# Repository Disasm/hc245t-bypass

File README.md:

# `hc245t-bypass`

This tiny board is useful to replace 74HC245T chips on Colorlight 5A-75B and 5A-75E boards.

You can order these boards from OSH Park: https://oshpark.com/shared_projects/Og8YtGBU Don't forget to select Flex board type on the order page!

## Rework

The board needs some rework to improve solderability. It's also possible to solder it "as is", but you can encounter shorts between the adjacent pins.

First, separate the boards from a panel. This can be done easily with scissors.

Next, cut each board by the line marked in red. The line should be on the edge of each via, not on the center. Try to make the line as straight as possible. The idea is to cut as much copper as possible, avoiding cutting most of the via copper.

Now solder it! Note that the first "pin" on the flex board corresponds to the second pin of the 74HC245T footpint.

You can also skip soldering about 50% of 74HC245T footprints by skipping footprints that are used for common signal (like A-E, CLK, LATCH, BLANK) distribution. You can learn in advance which footprints you need to solder and which not. Usually "color" signals are distributed through separate 74HC245T buffers located in groups of 3. Of course, this way you will not be able to control 8 signals out of... many, but it's still a good price for not soldering ~50% of tiny boards.

Additionally, you can use a continuity tester to check that all "data" pins are connected and adjacent pins are not shorted accidentally. Some of the 74HC245T footpints used for common signal distribution have some of the pins connected together. Check twice: probably your "ringing" footprint has some signals connected on purpose.

## Original work

Shoutouts to [Tom Keddie](https://twitter.com/tom_keddie), who made the [first prototype](https://twitter.com/tom_keddie/status/1233759892164362241) with OSH Park flex board process. Unfortunately, castellated vias on OSH Park flex boards are not officially supported, and they do not guarantee correct manufacturing for such vias. The board in this repo is the improved version of the prototype with the following changes:

* Traces are on both sides of the board instead of only the top side.
* Castellated vias aren't used, instead they are made during the rework process.
* 4 boards in a panel, instead of 2.
* Smaller silkscreen text that fits between the vias.

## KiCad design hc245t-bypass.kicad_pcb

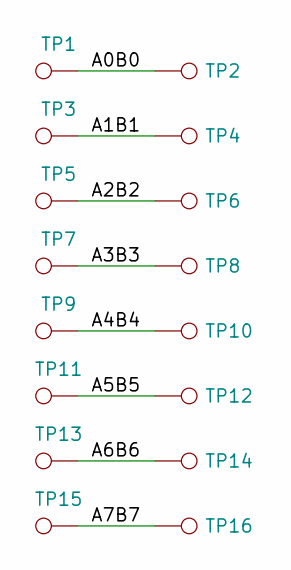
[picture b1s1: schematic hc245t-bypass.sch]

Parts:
TP1, TP2, TP3, TP4, TP5, TP6, TP7, TP8, TP9, TP10, TP11, TP12, TP13, TP14, TP15, TP16: TestPoint; PAD

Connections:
/A0B0: TP1.1, TP2.1
/A1B1: TP3.1, TP4.1
/A2B2: TP5.1, TP6.1
/A3B3: TP7.1, TP8.1
/A4B4: TP9.1, TP10.1
/A5B5: TP11.1, TP12.1
/A6B6: TP13.1, TP14.1
/A7B7: TP15.1, TP16.1

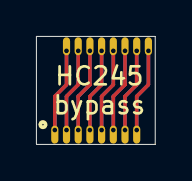
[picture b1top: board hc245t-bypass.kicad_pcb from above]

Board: 2 copper layers, 6.6 x 6.0 mm, 16 parts (0 on the bottom side), 8 nets.

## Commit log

2020-08-30 Add gerbers
2020-08-30 Add README.md
2020-08-30 Add the 'Original work' section
2020-08-30 Add warning about Flex type
2020-08-30 Add soldering instructions
2020-08-30 Mention the trick with common signal buffers
